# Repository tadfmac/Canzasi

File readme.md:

# Canzasi

「Canzasi」（かんざし）はArduinoを使ってI2C Slaveデバイスを試作するためのボードです。

# boards

## Canzasi-Prot

ATtiny841を採用した「Canzasi」最初のプロトタイプボードです。
Arduino IDEからISP経由での書き込みに対応しています。

### Concept

- Arduino IDE対応（ISP Programming）
- GROVEコネクタ
- ブレッドボードフレンドリー（1列GPIO）

### Design Data (v0.2)

[eagle files (v0.2)](./boards/Prot/v0.2/eagle/)

## Canzasi-Wrtr

Canzasi-Protにプログラムを書き込むためのArduino UNO用シールドです。

### Concept

- ミニマル
- Canzasi-Protとの接続にケーブル不要

### Design Data (v0.1)

[eagle files (v0.1)](./boards/Wrtr/v0.1/eagle/)

> v0.2に不具合 (#7) が見つかったため、一時的にstableをv0.1に戻しています。

## CHRMN-SimpleShield

Canzasiを搭載しいたCHIRIMEN用のシールドです。
外部に2つのGPIOしか出ていないこともあり、本ボードではATtiny841より安価なATtiny441を採用しています。

※写真はv0.1のものです。

### Concept

- 小さなフットプリントでCHIRIMENの基本的な実験に必要な機能を全て搭載

### Design Data (v0.2)

## Canzasi-Cont

CanzasiをベースにしたI2C接続ゲームパッドです。

### Concept

- ちいさい
- Groveコネクタで簡単に接続

### Design Data (v0.1)

[eagle files (v0.1)](./boards/Cont/v0.1/eagle/)

# examples

## [blink](./examples/blink/Canzasi_blink/Canzasi_blink.ino)

Canzasi用のLチカです。
これは単なるLチカで、I2Cデバイスではありません。

## [simpleAnalogDevice](./examples/simpleAnalogDevice/Canzasi/Canzasi_I2CAnalogDevice/Canzasi_I2CAnalogDevice.ino)

Masterからのread要求を受けてADC (10bit)の値を返すサンプルです。    
simpleAnalogDeviceを利用するマスターデバイスのサンプルコードはこちら（[Arduino用](./examples/simpleAnalogDevice/Master/Arduino/I2C_MasterWordReader/I2C_MasterWordReader.ino)）です。

## [simpleButtonDevice](./examples/simpleButtonDevice/Canzasi/Canzasi_I2CDataProvider/Canzasi_I2CDataProvider.ino)

Masterからのread要求を受けてButtonが押されているかどうかを返すサンプルです。    
simpleButtonDeviceを利用するマスターデバイスのサンプルコードはこちら（[Arduino用](./examples/simpleButtonDevice/Master/Arduino/I2C_MasterReader/I2C_MasterReader.ino)）です。

## [simpleLedDevice](./examples/simpleLedDevice/Canzasi/Canzasi_I2Cblink/Canzasi_I2Cblink.ino)

Masterからのwriteデータを受けてLEDの点灯と消灯を行うサンプルです。    
simpleLedDeviceを利用するマスターデバイスのサンプルコードはこちら（[Arduino用](./examples/simpleLedDevice/Master/Arduino/I2C_MasterWriter/I2C_MasterWriter.ino)）です。

## [combined_4_Analog_1](./examples/combined_4_Analog_1/Canzasi/Canzasi_combined_4_Analog_1/Canzasi_combined_4_Analog_1.ino)

4つのアナログボリューム（可変抵抗）を接続したデバイスです。
Masterからのwrite 1byte（4つのアナログボリュームのどの値を返すかを指定）の後にSRを経由した Read 1byteに対応して8bitのアナログボリュームのデータを返します。

combined_4_Analog_1を利用するマスターデバイスのサンプルコードはこちら（[CHIRIMEN用](./examples/combined_4_Analog_1/Master/chirimen/)）です。

## [combined_4_Analog_2](./examples/combined_4_Analog_2/Canzasi/Canzasi_combined_4_Analog_2/Canzasi_combined_4_Analog_2.ino)

4つのアナログボリューム（可変抵抗）を接続したデバイスです。
Masterからのwrite 1byte（4つのアナログボリュームを2つづつのセットにして、グループA、Bどちらの値を返すかを指定）の後にSRを経由した Read 2byteに対応して8bitのアナログボリューム2つ分のデータを返します。

combined_4_Analog_2を利用するマスターデバイスのサンプルコードはこちら（[CHIRIMEN用](./examples/combined_4_Analog_2/Master/chirimen/)）です。

# Licence

<br />このリポジトリで公開するプログラムソースコードやハードウエア設計情報は <a rel="license" href="http://creativecommons.org/licenses/by/4.0/">クリエイティブ・コモンズ 表示 4.0 国際 ライセンスの下に提供されています。</a>

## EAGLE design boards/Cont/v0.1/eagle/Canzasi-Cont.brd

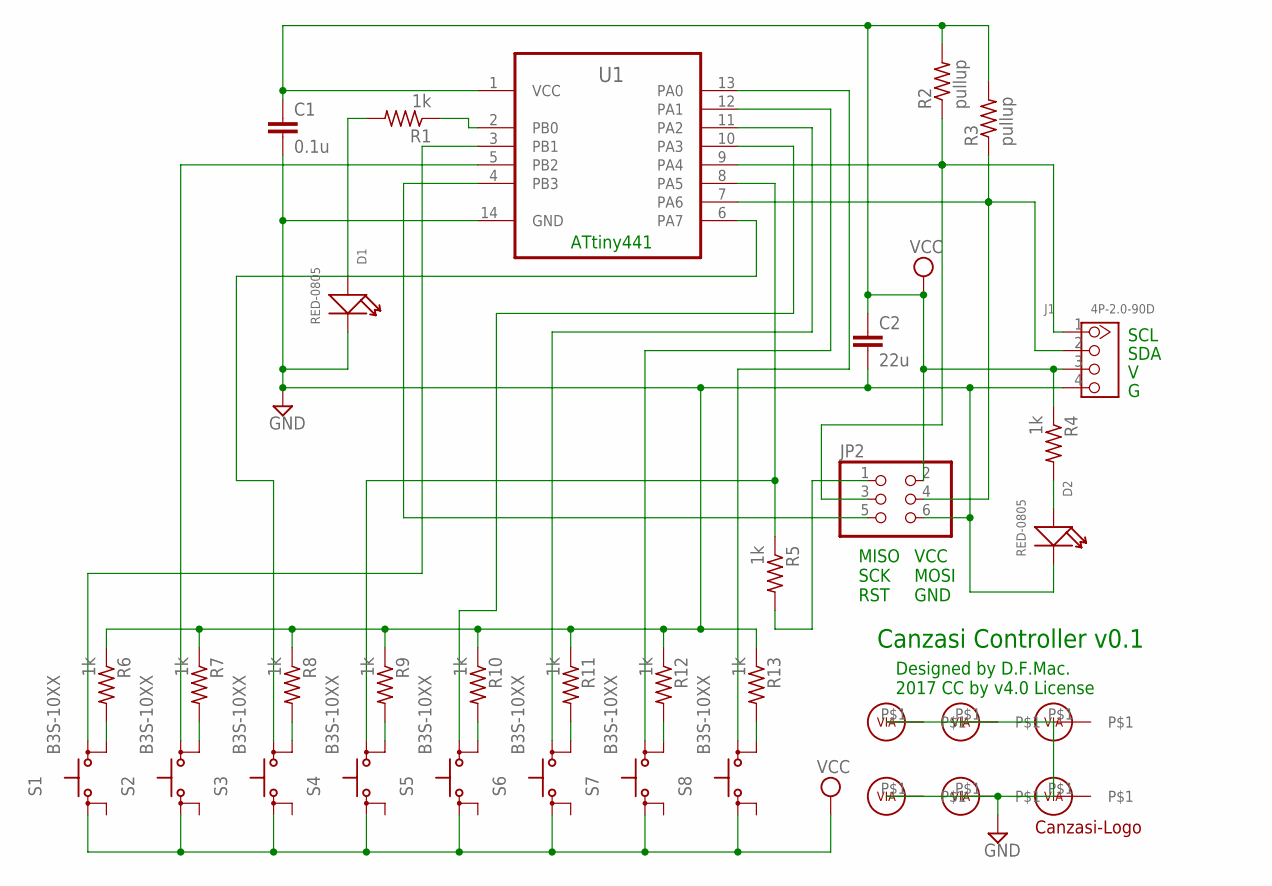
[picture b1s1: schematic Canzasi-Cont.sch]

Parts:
C1: 0.1u; C0603
C2: 22u; C0805
D1, D2: RED-0805; LED-0805
J1: 4P-2.0-90D; HW4-2.0-90D
JP2: PINHD-2X3; 2X03
R1, R4, R5, R6, R7, R8, R9, R10, R11, R12, R13: 1k; R0603
R2, R3: pullup; R0603
S1, S2, S3, S4, S5, S6, S7, S8: B3S-10XX
U1: ATTINY44A-SSU; SOIC127P600X175-14N
U$1: CANZASI-LOGOMEDIUM; CANZASI-LOGO-MEDIUM
U$2, U$3, U$4, U$5, U$6, U$7: VIA

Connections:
GND: C1.2, C2.2, D1.-, D2.-, J1.4, JP2.6, R6.1, R7.1, R8.1, R9.1, R10.1, R11.1, R12.1, R13.1, U1.14 (GND), U$2.P$1, U$3.P$1, U$4.P$1, U$5.P$1, U$6.P$1, U$7.P$1
unnamed: R1.1, U1.2 (PB0)
unnamed: D1.+, R1.2
unnamed: J1.2, JP2.4, R3.1, U1.7 (PA6)
unnamed: J1.1, JP2.3, R2.1, U1.9 (PA4)
unnamed: S1.3 (S), U1.3 (PB1)
unnamed: S2.3 (S), U1.5 (PB2)
unnamed: JP2.5, U1.4 (PB3)
unnamed: S3.3 (S), U1.6 (PA7)
unnamed: R5.1, S4.3 (S), U1.8 (PA5)
unnamed: S5.3 (S), U1.10 (PA3)
unnamed: S6.3 (S), U1.11 (PA2)
unnamed: S7.3 (S), U1.12 (PA1)
unnamed: S8.3 (S), U1.13 (PA0)
unnamed: D2.+, R4.2
unnamed: JP2.1, R5.2
unnamed: R6.2, S1.4 (S1)
unnamed: R7.2, S2.4 (S1)
unnamed: R8.2, S3.4 (S1)
unnamed: R9.2, S4.4 (S1)
unnamed: R10.2, S5.4 (S1)
unnamed: R11.2, S6.4 (S1)
unnamed: R12.2, S7.4 (S1)
unnamed: R13.2, S8.4 (S1)
VCC: C1.1, C2.1, J1.3, JP2.2, R2.2, R3.2, R4.1, S1.1, S2.1, S3.1, S4.1, S5.1, S6.1, S7.1, S8.1, U1.1 (VCC)

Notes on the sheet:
SCL
SDA
MISO SCK RST
VCC MOSI GND
ATtiny441
Canzasi Controller v0.1
Designed by D.F.Mac. 2017 CC by v4.0 License

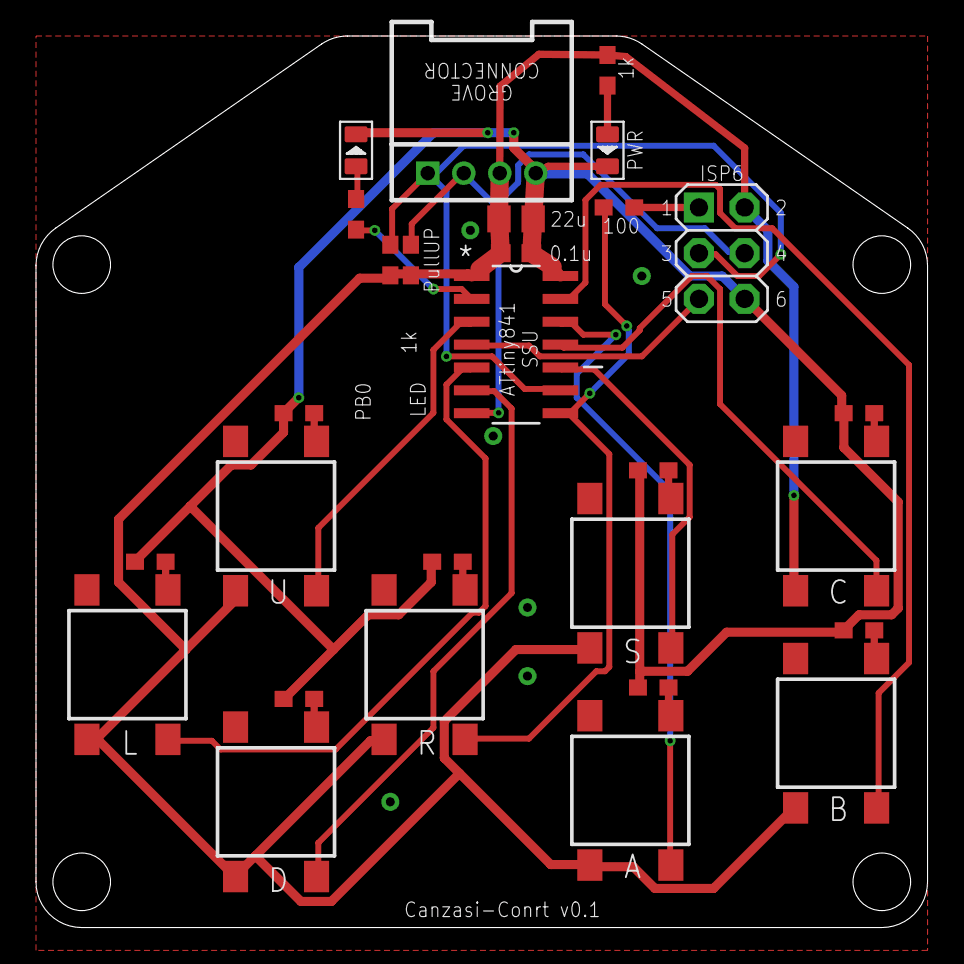
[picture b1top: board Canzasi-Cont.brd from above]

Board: 2 copper layers, 49.5 x 49.5 mm, 35 parts (1 on the bottom side), 25 nets.

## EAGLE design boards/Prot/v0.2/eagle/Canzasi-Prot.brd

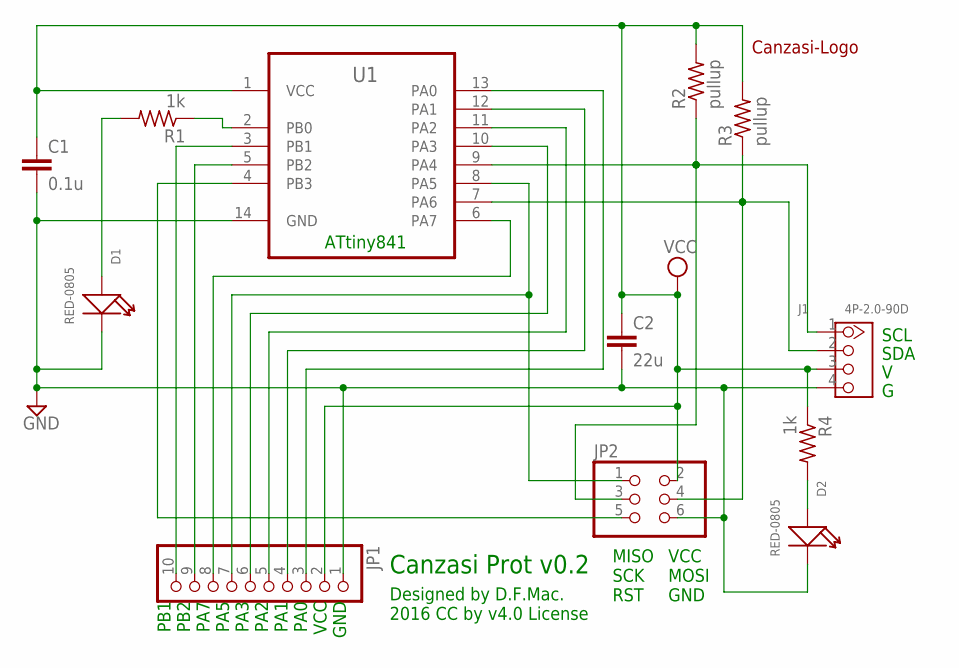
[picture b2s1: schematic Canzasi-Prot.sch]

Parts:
C1: 0.1u; C0603
C2: 22u; C0805
D1, D2: RED-0805; LED-0805
J1: 4P-2.0-90D; HW4-2.0-90D
JP1: PINHD-1X10; 1X10
JP2: PINHD-2X3; 2X03
R1, R4: 1k; R0603
R2, R3: pullup; R0603
U1: ATTINY44A-SSU; SOIC127P600X175-14N
U$1: CANZASI-LOGOMEDIUM; CANZASI-LOGO-MEDIUM

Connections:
GND: C1.2, C2.2, D1.-, D2.-, J1.4, JP1.1, JP2.6, U1.14 (GND)
unnamed: R1.1, U1.2 (PB0)
unnamed: D1.+, R1.2
unnamed: J1.2, JP2.4, R3.1, U1.7 (PA6)
unnamed: J1.1, JP2.3, R2.1, U1.9 (PA4)
unnamed: JP1.10, U1.3 (PB1)
unnamed: JP1.9, U1.5 (PB2)
unnamed: JP2.5, U1.4 (PB3)
unnamed: JP1.8, U1.6 (PA7)
unnamed: JP1.7, JP2.1, U1.8 (PA5)
unnamed: JP1.6, U1.10 (PA3)
unnamed: JP1.5, U1.11 (PA2)
unnamed: JP1.4, U1.12 (PA1)
unnamed: JP1.3, U1.13 (PA0)
unnamed: D2.+, R4.2
VCC: C1.1, C2.1, J1.3, JP1.2, JP2.2, R2.2, R3.2, R4.1, U1.1 (VCC)

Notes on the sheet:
SCL
SDA
MISO SCK RST
VCC MOSI GND
PB1 PB2 PA7 PA5 PA3 PA2 PA1 PA0 VCC GND
ATtiny841
Canzasi Prot v0.2
Designed by D.F.Mac. 2016 CC by v4.0 License

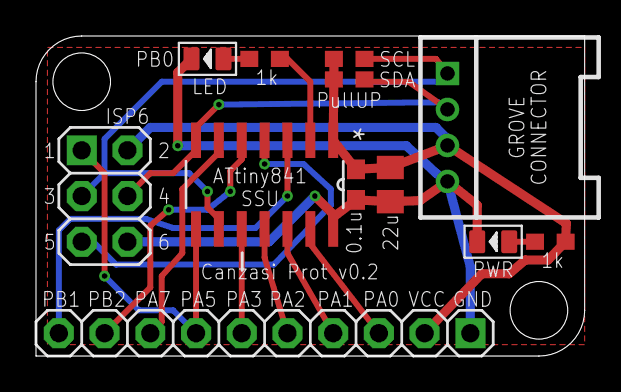
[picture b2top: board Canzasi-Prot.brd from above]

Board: 2 copper layers, 30.5 x 17.8 mm, 13 parts (1 on the bottom side), 16 nets.

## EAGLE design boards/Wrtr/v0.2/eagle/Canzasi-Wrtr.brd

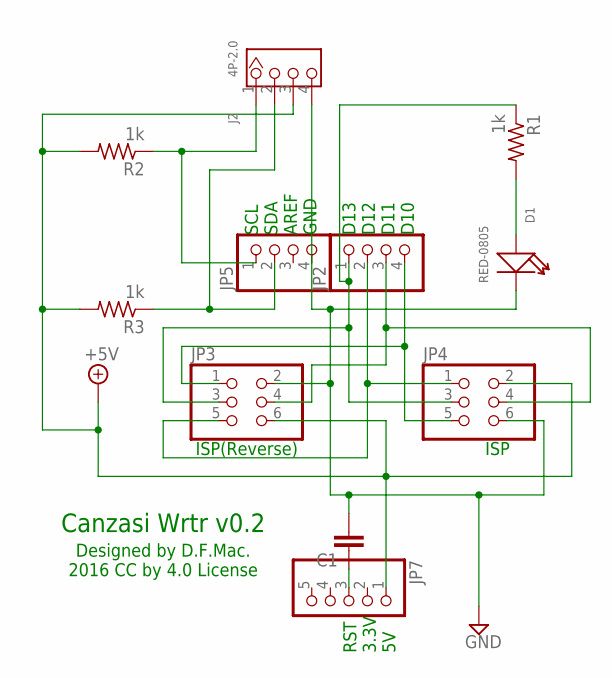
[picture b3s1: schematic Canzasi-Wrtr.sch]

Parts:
C1: C-EUC0805; C0805
D1: RED-0805; LED-0805
J2: 4P-2.0; HW4-2.0
JP2, JP5: PINHD-1X4; 1X04
JP3, JP4: PINHD-2X3; 2X03
JP7: PINHD-1X5; 1X05
R1, R2, R3: 1k; R0603

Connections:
+5V: J2.3, JP3.6, JP4.2, JP7.1, R2.2, R3.2
GND: C1.2, D1.-, J2.4, JP3.2, JP4.6, JP5.4
unnamed: JP2.4, JP3.1, JP4.5
unnamed: C1.1, JP7.3
unnamed: J2.1, JP5.1, R2.1
unnamed: JP2.1, JP3.3, JP4.3, R1.1
unnamed: JP2.2, JP3.5, JP4.1
unnamed: JP2.3, JP3.4, JP4.4
unnamed: J2.2, JP5.2, R3.1
unnamed: D1.+, R1.2

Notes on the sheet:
RST 3.3V 5V
SCL SDA AREF GND D13 D12 D11 D10
ISP
ISP(Reverse)
Canzasi Wrtr v0.2
Designed by D.F.Mac. 2016 CC by 4.0 License

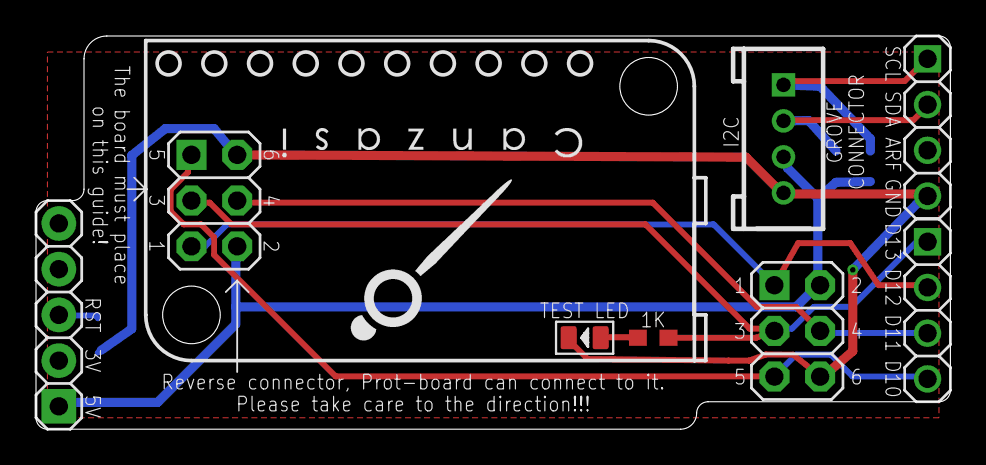
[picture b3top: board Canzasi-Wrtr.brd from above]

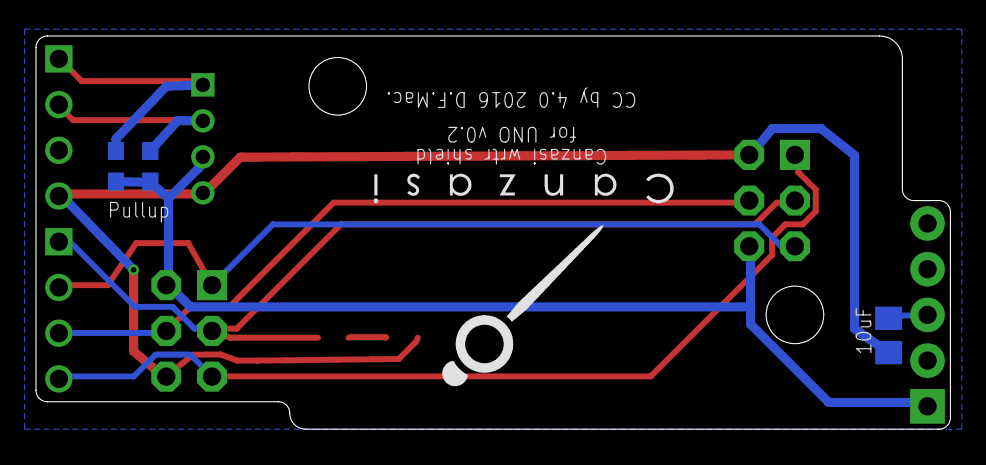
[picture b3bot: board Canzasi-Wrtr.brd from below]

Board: 2 copper layers, 50.8 x 21.8 mm, 13 parts (4 on the bottom side), 10 nets.

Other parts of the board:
U$1, U$2: CANZASI-LOGOMEDIUM; CANZASI-LOGO-MEDIUM

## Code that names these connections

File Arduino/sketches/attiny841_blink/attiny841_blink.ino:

// Blink for Canzasi-Prot(ATtiny841)
// with https://github.com/SpenceKonde/ATTinyCore
// 
// License CC by 4.0 2016 D.F.Mac.
//
//                   +----+
//                VCC|    |GND
// LED    PB0/A11/ D0|    |D10/A0 /PA0
//        PB1/A10/ D1|    |D9 /A1 /PA1
//        PB3/ A9/D11|    |D8 /A2 /PA2
//        PB2/ A8/ D2|    |D7 /A3 /PA3
//        PA7/ A7/ D3|    |D6 /A4 /PA4
//        PA6/ A6/ D4|    |D5 /A5 /PA5
//                   +----+
//

#define LED_PIN 0 // PB0

void setup() {
  // put your setup code here, to run once:
  pinMode(LED_PIN,OUTPUT);
}

void loop() {
  // put your main code here, to run repeatedly:
  digitalWrite(LED_PIN,HIGH);
  delay(1000);
  digitalWrite(LED_PIN,LOW);
  delay(1000);
}

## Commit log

2016-10-14 add sketch data
2016-10-14 wip: 10/14 buckup
2016-10-15 revise icons
2016-10-16 add Prot board info(v0.1)
2016-10-16 add Canzasi-logo-small-m.png
2016-10-18 revise samples and fix library
2016-10-18 add first examples
2016-10-18 add Wrtr v0.1
2016-10-21 revise examples
2016-10-28 Prot/Wrtr : update v0.2 (fix issue #5)
2016-11-03 add example for analog devices
2016-11-04 examples: add multiFunctionalAnalogDevice
2016-11-11 wrtr stable rollback to v0.1
2016-12-13 i2c841s2.h: fix bug
2017-01-04 add combined examples
2017-01-12 add ATtiny441 Support
2017-01-12 add SimpleShield desc (WIP)
2017-03-23 add SimpleShield design data
2017-05-26 add Canzasi-Cont v0.1 files
